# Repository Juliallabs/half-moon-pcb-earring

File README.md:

## ⭐ Half Moon Earring

Este projeto é uma placa de circuito impresso artística que pode ser utilizada como um brinco ou chaveiro. Esta placa foi desenvolvida usando o software [Eagle](https://www.autodesk.com/products/eagle/overview).

Essa placa foi projetada no formato de meia lua e possui um sensor de toque capacitivo que permite que os LEDs da placa sejam ligados e desligados.

## 📝 Esquemático

## ⚙️ Componentes necessários para o projeto (BOM LIST)

A lista de componentes necessários para a montagem desta placa está listado abaixo:

|           Descrição           | Quantidade |     Posição      |    Part Number     |
| :---------------------------: | :--------: | :--------------: | :----------------: |
|      CAPACITOR 22pF 0805      |     1      |        C1        | YFF21AC1H220MT0Y0N |
|      RESISTOR 150R 0805       |     2      |      R1,R2       |  TNPW0805150RFEEA  |
|       TRANSISTOR BC817        |     1      |        T1        |    BC817K-16HR     |
|        LED 5050 YELLOW        |     3      | LED1, LED2, LED3 |  SML-LX5050SYC-TR  |
| KEY TOUCH PAD DETECTOR TTP223 |     1      |       IC1        |    TTP223N-BA6     |
| COIN CELL BATTERY HOLDER 2025 |     1      |       PW1        |    BAT-HLD-001     |

## 🤝 Parcerias

Este projeto foi desenvolvido em parceria com:

## 📹 Vídeos relacionados

Veja alguns vídeos que produzi relacionados a este projeto:

-   [MINHA COLEÇÃO DE PLACAS DE CIRCUITO IMPRESSO](https://www.youtube.com/watch?v=9CJyRkSh-_w)
-   [Com o que eu TRABALHO sendo ENGENHEIRA DE COMPUTAÇÃO??](https://www.youtube.com/watch?v=FRl2C3OQMmk)
-   [PROJETOS QUE DESENVOLVEMOS EM 2021!!](https://www.youtube.com/watch?v=Xe8zhBSLv80)
-   [🤓Quando uma ENGENHEIRA decide fazer um BRINCO 🤓](https://www.youtube.com/watch?v=Eptdd2IPP_g)

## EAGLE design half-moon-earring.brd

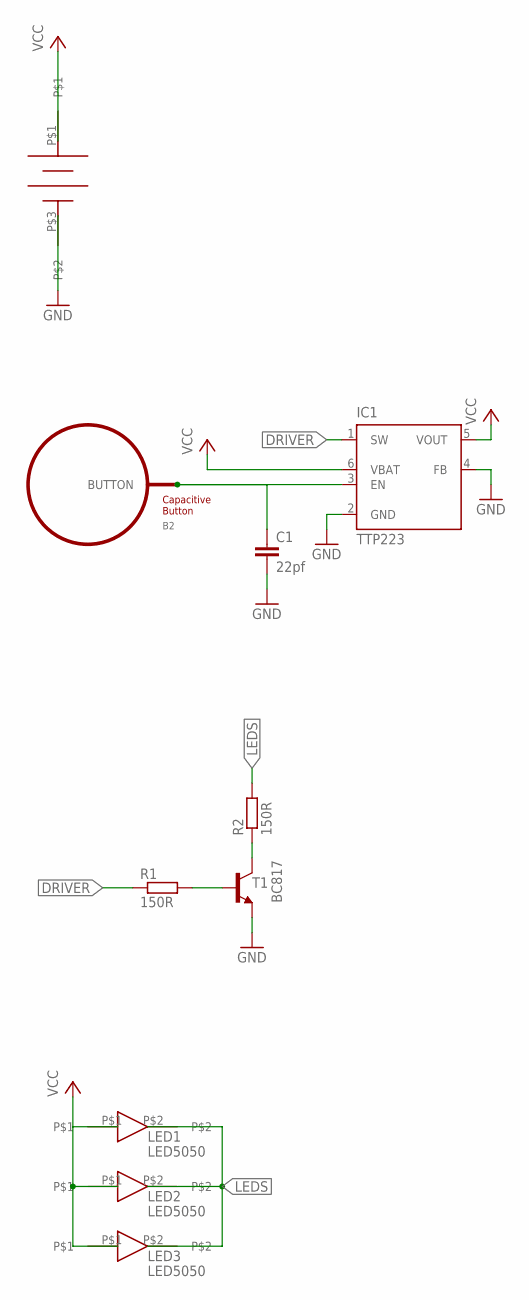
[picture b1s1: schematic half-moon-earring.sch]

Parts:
B2: BUTTON_PASSIVE8MM; BUTTON_PASSIVE_8MM
C1: 22pf; C0805
IC1: TTP223; TSOT23-6_DDC
LED1, LED2, LED3: LED5050
PW1: CR2025 BATERY HOLDER; CR2025
R1, R2: 150R; M0805
T1: BC817; SOT23-BEC

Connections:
DRIVER: IC1.1 (SW), R1.1
GND: C1.2, IC1.2 (GND), IC1.4 (FB), PW1.P$3, T1.E; also elsewhere on the board
LEDS: LED1.P$2, LED2.P$2, LED3.P$2, R2.2
unnamed: R1.2, T1.B
unnamed: R2.1, T1.C
unnamed: B2.BUTTON, C1.1, IC1.3 (EN)
VCC: IC1.5 (VOUT), IC1.6 (VBAT), LED1.P$1, LED2.P$1, LED3.P$1, PW1.P$1; also elsewhere on the board

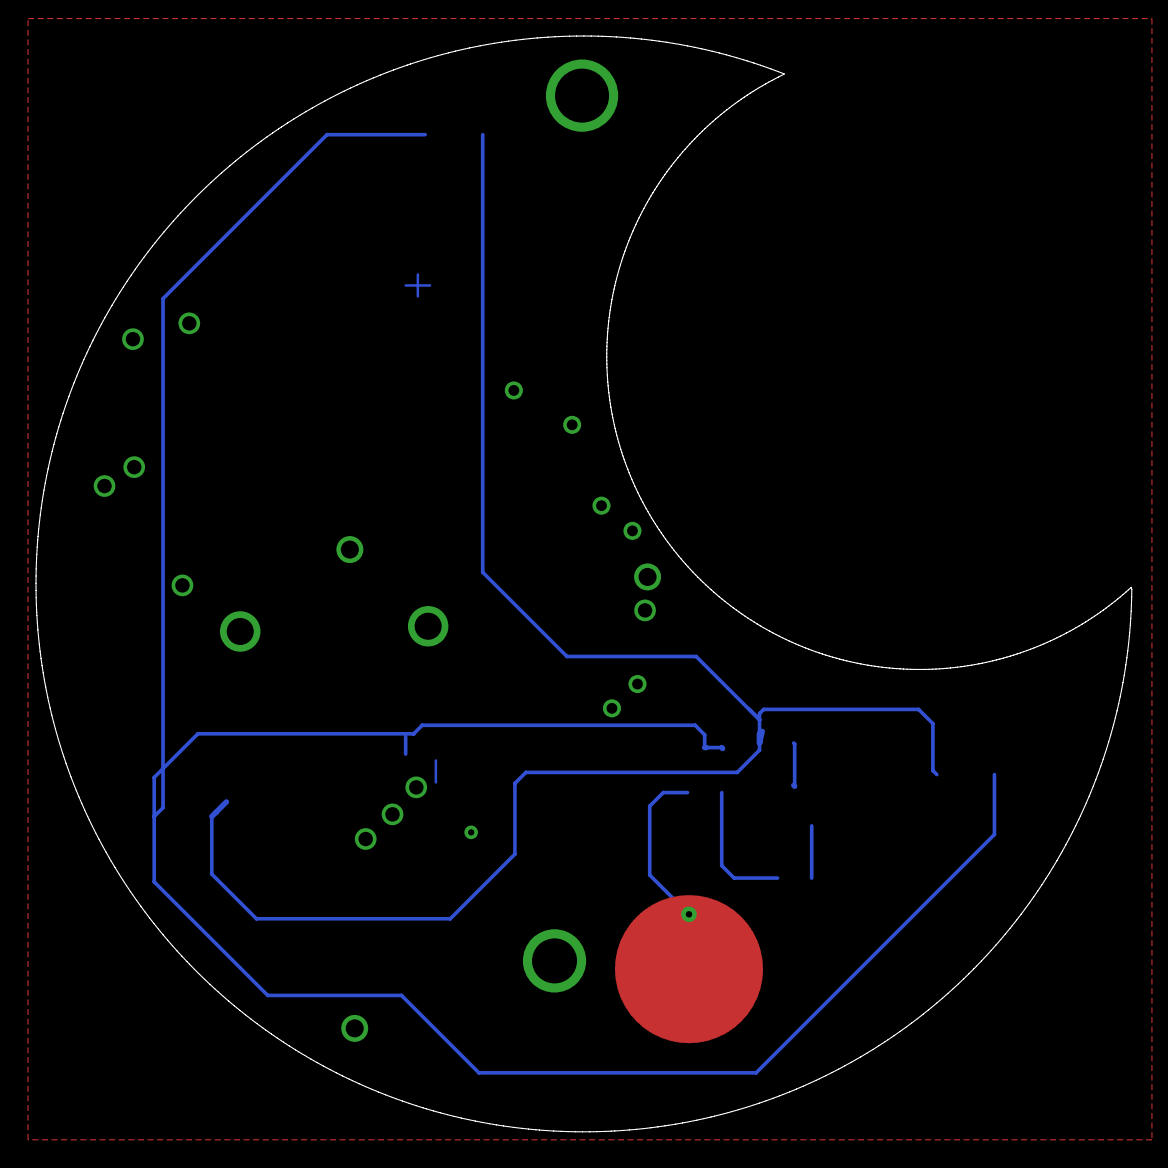
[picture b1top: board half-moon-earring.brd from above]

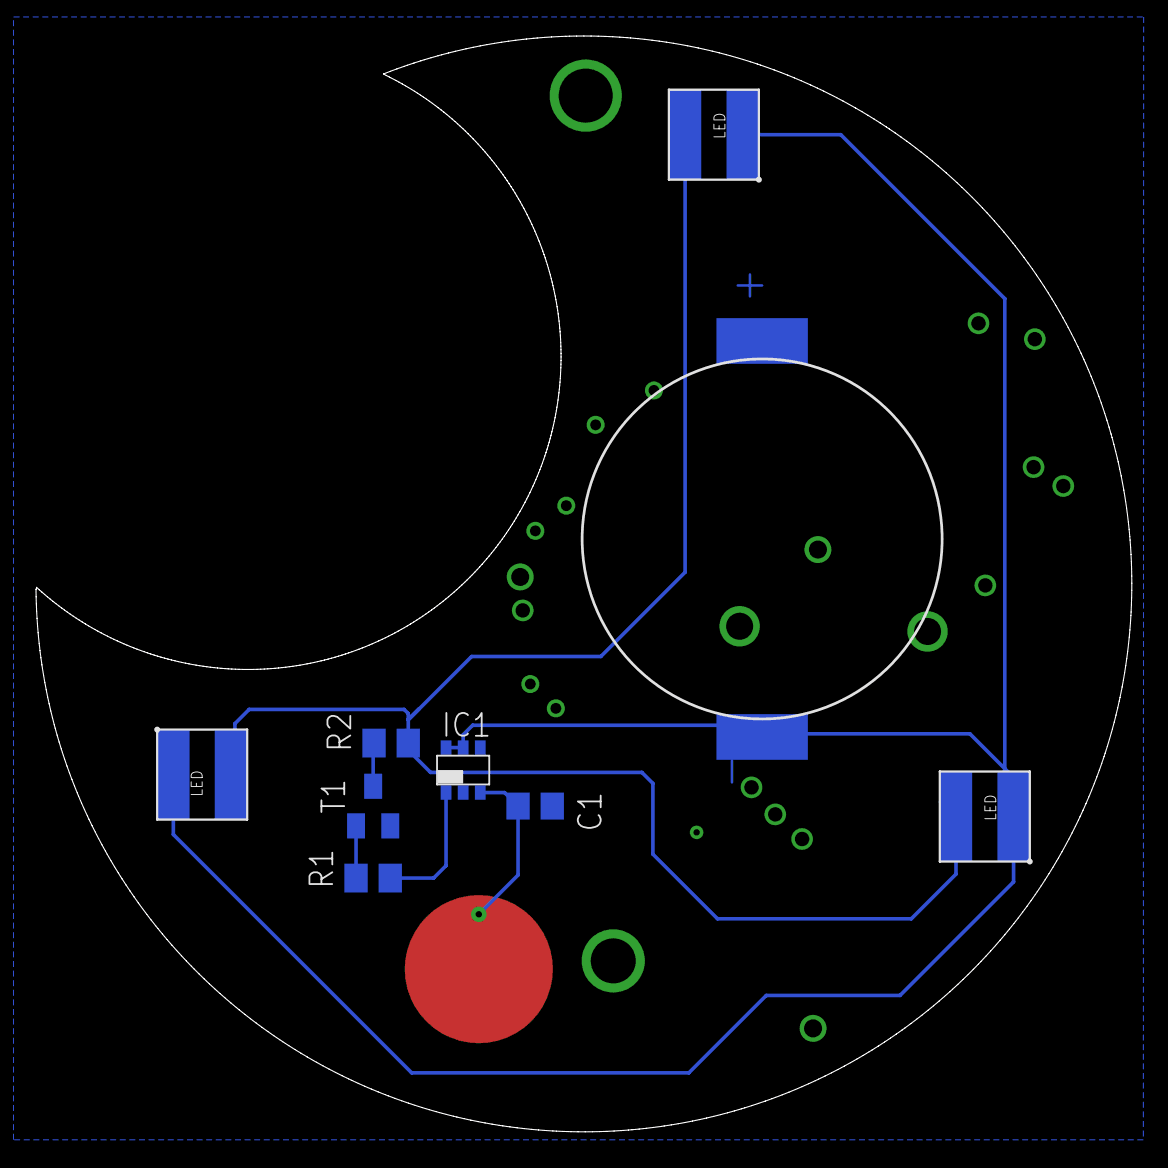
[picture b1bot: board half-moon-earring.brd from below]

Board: 2 copper layers, 60.9 x 60.9 mm, 10 parts (9 on the bottom side), 7 nets.

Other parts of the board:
U$1: CR2035

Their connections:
GND: U$1.P$2; also elsewhere on the board
VCC: U$1.P$1; also elsewhere on the board

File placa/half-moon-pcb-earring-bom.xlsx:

BOM LIST HALF-MOON PCB EARRING
DESCRIPTION | QUANTITY | POSITION | PART NUMBER
CAPACITOR 22pF 0805 | 1 | C1 | YFF21AC1H220MT0Y0N, can be replaced to similar
RESISTOR 150R 0805 | 2 | R1,R2 | TNPW0805150RFEEA, can be replaced to similar
TRANSISTOR BC817 | 1 | T1 | BC817K-16HR, can be replaced to similar
LED 5050 YELLOW | 3 | LED1, LED2, LED3 | SML-LX5050SYC-TR, can be replaced to similar
KEY TOUCH PAD DETECTOR TTP223 | 1 | IC1 | TTP223N-BA6
COIN CELL BATTERY HOLDER 2025 | 1 | PW1 | BAT-HLD-001

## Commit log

2020-11-03 init project
2020-11-03 com logo github
2020-11-03 ignore files
2020-11-12 deletando arquivos inuteis
2020-11-13 um teste
2020-11-21 bom list
2021-03-22 correção de tamanho
2023-07-08 Organização em pastas
2023-07-08 Primeira versão do README

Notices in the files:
parts and their libraries:
PatternAgents-TouchWidgets: License : http://creativecommons.org/licenses/by-sa/4.0/ (Creative Commons 4.0)
PatternAgents-TouchWidgets: License : http://creativecommons.org/licenses/by-sa/3.1/ (Creative Commons 3.1)
